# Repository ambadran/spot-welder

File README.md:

Battery Spot Welder Circuit Using Capactive Discharge (CD) Circuit

Using PIC16F628A and 16x2 display, a user-friendly interface is implemented

Three lines of capacitors (six in series) circuit act as the capacitor bank for HIGH
current discharge. They total to a <> Coloumbs.
They have an equivilant series resistance of <> milli-ohms
This means that at 24v they can deliver <> Amps!!!

Four VERY HIGH Power MOSFETs IRF3205 are put in parallel, capable of withstanding <> Amps through them

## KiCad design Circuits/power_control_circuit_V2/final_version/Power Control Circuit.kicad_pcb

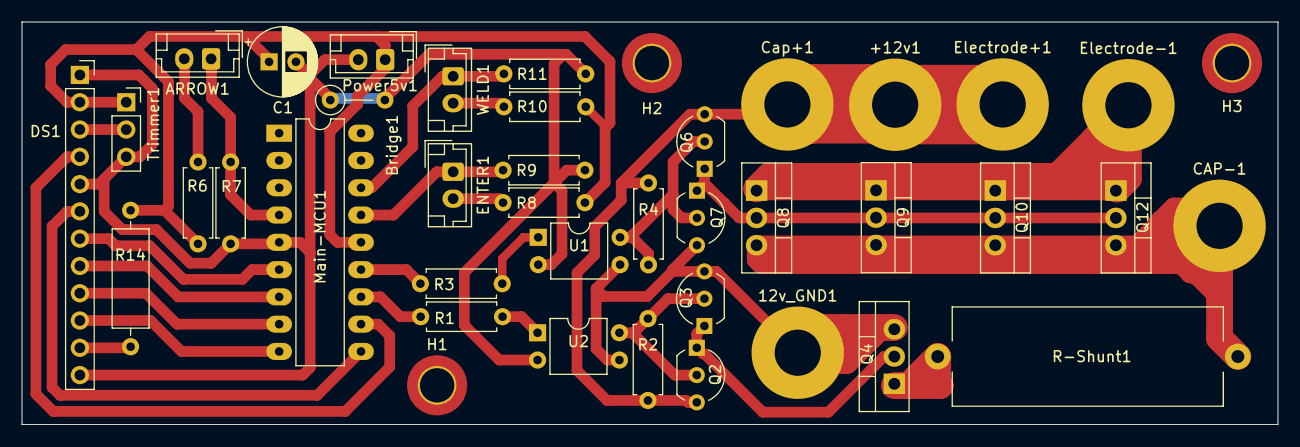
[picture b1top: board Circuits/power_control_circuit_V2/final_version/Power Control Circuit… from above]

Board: 2 copper layers, 116.9 x 37.5 mm, 41 parts (0 on the bottom side), 29 nets.

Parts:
12v_GND1: Pin; MountingHole_4.3mm_M4_Pad
+12v1: Pin; MountingHole_4.3mm_M4_Pad
ARROW1: JST-2P; JST_EH_B2B-EH-A_1x02_P2.50mm_Vertical
Bridge1: 0ohm; R_Axial_DIN0207_L6.3mm_D2.5mm_P5.08mm_Vertical
C1: 220uF; CP_Radial_D6.3mm_P2.50mm
CAP-1: Pin; MountingHole_4.3mm_M4_Pad
Cap+1: Pin; MountingHole_4.3mm_M4_Pad
DS1: WC1602A; PinSocket_1x12_P2.54mm_Vertical
ENTER1: JST-2P; JST_EH_B2B-EH-A_1x02_P2.50mm_Vertical
Electrode+1: Pin; MountingHole_4.3mm_M4_Pad
Electrode-1: Pin; MountingHole_4.3mm_M4_Pad
H1, H2, H3: MountingHole; MountingHole_3.2mm_M3_DIN965_Pad_TopBottom
Main-MCU1: PIC16F628A-IP; DIP-18_W7.62mm_LongPads
Power5v1: JST-2P; JST_EH_B2B-EH-A_1x02_P2.50mm_Vertical
Q2, Q6: S8050; TO-92_Inline_Wide
Q3, Q7: S8550; TO-92_Inline_Wide
Q4, Q8, Q9, Q10, Q12: IRF1405; TO-220-3_Vertical
R1, R3: 220; R_Axial_DIN0207_L6.3mm_D2.5mm_P7.62mm_Horizontal
R2, R4, R6, R8, R10: 1k; R_Axial_DIN0207_L6.3mm_D2.5mm_P7.62mm_Horizontal
R7, R9, R11: 10k; R_Axial_DIN0207_L6.3mm_D2.5mm_P7.62mm_Horizontal
R14: 330; R_Axial_DIN0309_L9.0mm_D3.2mm_P12.70mm_Horizontal
R-Shunt1: 2ohm; R_Axial_Power_L25.0mm_W9.0mm_P27.94mm
Trimmer1: 5kOhm; PinSocket_1x03_P2.54mm_Vertical
U1, U2: PC817; DIP-4_W7.62mm
WELD1: JST-2P; JST_EH_B2B-EH-A_1x02_P2.50mm_Vertical

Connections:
+5V: C1.1, DS1.2 (VDD), Main-MCU1.14 (VDD), Power5v1.1, R6.1, R8.1, R10.1, R14.1, Trimmer1.1
+12V: +12v1.1, Cap+1.1, Electrode+1.1, Q2.3 (C), Q6.3 (C), R2.1, R4.1
/NMOS_CHARGE: Q4.1 (D), R-Shunt1.1
/NMOS_DISCHARGE: Electrode-1.1, Q8.1 (D), Q9.1 (D), Q10.1 (D), Q12.1 (D)
Charging: Main-MCU1.12 (RB6/T1OSC0/T1CKI/PGC), R1.2
D4: DS1.7 (D4), Main-MCU1.6 (RB0/INT)
D5: DS1.8 (D5), Main-MCU1.7 (RB1/RX/DT)
D6: DS1.9 (D6), Main-MCU1.8 (RB2/TX/CK)
D7: DS1.10 (D7), Main-MCU1.9 (RB3/CCP1)
Discharge: Main-MCU1.13 (RB7/T1OSI/PGD), R3.2
EN: DS1.6 (E), Main-MCU1.10 (RB4/PGM)
GND: Bridge1.1, Bridge1.2, C1.2, DS1.1 (VSS), DS1.5 (R/W), DS1.12 (LED(-)), Main-MCU1.5 (VSS), Power5v1.2, R7.2, R9.2, R11.2, Trimmer1.3, U1.2, U2.2
GNDA: 12v_GND1.1, Q3.3 (C), Q4.3 (S), Q7.3 (C), U1.3, U2.3
GNDS: CAP-1.1, Q8.3 (S), Q9.3 (S), Q10.3 (S), Q12.3 (S), R-Shunt1.2
unnamed: ARROW1.2, R6.2
unnamed: DS1.11 (LED(+)), R14.2
unnamed: DS1.3 (VO), Trimmer1.2
unnamed: ENTER1.2, R8.2
unnamed: Q2.2 (B), Q3.2 (B), R2.2, U2.4
unnamed: Q2.1 (E), Q3.1 (E), Q4.2 (G)
unnamed: Q6.2 (B), Q7.2 (B), R4.2, U1.4
unnamed: Q6.1 (E), Q7.1 (E), Q8.2 (G), Q9.2 (G), Q10.2 (G), Q12.2 (G)
unnamed: R1.1, U2.1
unnamed: R3.1, U1.1
unnamed: R10.2, WELD1.2
RS: DS1.4 (RS), Main-MCU1.11 (RB5)
arrowkey: ARROW1.1, Main-MCU1.4 (~MCLR/Vpp/RA5), R7.1
enterkey: ENTER1.1, Main-MCU1.15 (CLKOUT/OSC2/RA6), R9.1
weldingkey: Main-MCU1.16 (CLKIN/OSC1/RA7), R11.1, WELD1.1

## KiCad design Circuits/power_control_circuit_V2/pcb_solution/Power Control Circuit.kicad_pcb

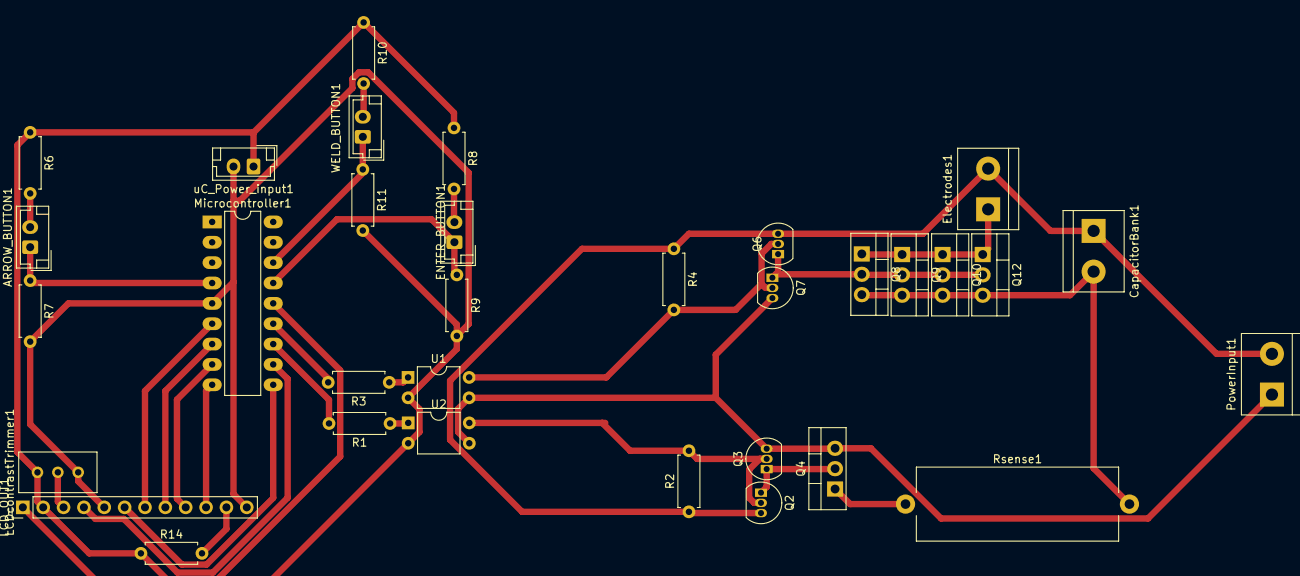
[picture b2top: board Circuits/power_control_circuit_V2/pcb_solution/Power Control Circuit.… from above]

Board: 2 copper layers, 33 parts (0 on the bottom side), 29 nets.

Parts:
ARROW_BUTTON1: Conn_01x02_Socket; JST_EH_B2B-EH-A_1x02_P2.50mm_Vertical
CapacitorBank1: CP; TerminalBlock_bornier-2_P5.08mm
ENTER_BUTTON1: Conn_01x02_Socket; JST_EH_B2B-EH-A_1x02_P2.50mm_Vertical
Electrodes1: Conn_01x02_Male; TerminalBlock_bornier-2_P5.08mm
LCD_OUT1: Conn_01x12_Socket; PinHeader_1x12_P2.54mm_Vertical
LCDcontrastTrimmer1: 5kOhm; Potentiometer_Bourns_3386C_Horizontal
Microcontroller1: PIC16F628A-IP; DIP-18_W7.62mm_LongPads
PowerInput1: Screw_Terminal_01x02; TerminalBlock_bornier-2_P5.08mm
Q2, Q6: S8050; TO-92_Inline
Q3, Q7: S8550; TO-92_Inline
Q4, Q8, Q9, Q10, Q12: IRF1405; TO-220-3_Vertical
R1, R3: 220; R_Axial_DIN0207_L6.3mm_D2.5mm_P7.62mm_Horizontal
R2, R4, R6, R8, R10: 1k; R_Axial_DIN0207_L6.3mm_D2.5mm_P7.62mm_Horizontal
R7, R9, R11: 10k; R_Axial_DIN0207_L6.3mm_D2.5mm_P7.62mm_Horizontal
R14: 330; R_Axial_DIN0207_L6.3mm_D2.5mm_P7.62mm_Horizontal
Rsense1: 1; R_Axial_Power_L25.0mm_W9.0mm_P27.94mm
U1, U2: PC817; DIP-4_W7.62mm
WELD_BUTTON1: Conn_01x02_Socket; JST_EH_B2B-EH-A_1x02_P2.50mm_Vertical
uC_Power_input1: Conn_01x02_Socket; JST_EH_B2B-EH-A_1x02_P2.50mm_Vertical

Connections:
+5V: LCD_OUT1.2, LCDcontrastTrimmer1.1, Microcontroller1.14 (VDD), R6.1, R8.1, R10.1, R14.1, uC_Power_input1.1
+12V: CapacitorBank1.1, Electrodes1.2, PowerInput1.2, Q2.3 (C), Q6.3 (C), R2.1, R4.1
Charging: Microcontroller1.12 (RB6/T1OSC0/T1CKI/PGC), R1.2
D4: LCD_OUT1.7, Microcontroller1.6 (RB0/INT)
D5: LCD_OUT1.8, Microcontroller1.7 (RB1/RX/DT)
D6: LCD_OUT1.9, Microcontroller1.8 (RB2/TX/CK)
D7: LCD_OUT1.10, Microcontroller1.9 (RB3/CCP1)
Discharge: Microcontroller1.13 (RB7/T1OSI/PGD), R3.2
EN: LCD_OUT1.6, Microcontroller1.10 (RB4/PGM)
GND: LCD_OUT1.1, LCD_OUT1.5, LCD_OUT1.12, LCDcontrastTrimmer1.3, Microcontroller1.5 (VSS), R7.2, R9.2, R11.2, U1.2, U2.2, uC_Power_input1.2
GNDA: PowerInput1.1, Q3.3 (C), Q4.3 (S), Q7.3 (C), U1.3, U2.3
GNDS: CapacitorBank1.2, Q8.3 (S), Q9.3 (S), Q10.3 (S), Q12.3 (S), Rsense1.2
LED+: LCD_OUT1.11, R14.2
unnamed: ARROW_BUTTON1.2, R6.2
unnamed: ENTER_BUTTON1.2, R8.2
unnamed: Electrodes1.1, Q8.1 (D), Q9.1 (D), Q10.1 (D), Q12.1 (D)
unnamed: Q2.2 (B), Q3.2 (B), R2.2, U2.4
unnamed: Q2.1 (E), Q3.1 (E), Q4.2 (G)
unnamed: Q4.1 (D), Rsense1.1
unnamed: Q6.2 (B), Q7.2 (B), R4.2, U1.4
unnamed: Q6.1 (E), Q7.1 (E), Q8.2 (G), Q9.2 (G), Q10.2 (G), Q12.2 (G)
unnamed: R1.1, U2.1
unnamed: R3.1, U1.1
unnamed: R10.2, WELD_BUTTON1.2
RS: LCD_OUT1.4, Microcontroller1.11 (RB5)
VO: LCD_OUT1.3, LCDcontrastTrimmer1.2
arrowkey: ARROW_BUTTON1.1, Microcontroller1.4 (~MCLR/Vpp/RA5), R7.1
enterkey: ENTER_BUTTON1.1, Microcontroller1.15 (CLKOUT/OSC2/RA6), R9.1
weldingkey: Microcontroller1.16 (CLKIN/OSC1/RA7), R11.1, WELD_BUTTON1.1

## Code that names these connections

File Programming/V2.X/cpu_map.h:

#ifndef CPU_MAP_H
#define CPU_MAP_H

/* **** LCD PINs **** */
#define LCD_DATA_TRIS TRISB
#define LCD_DATA PORTB
#define D4 RB0
#define D5 RB1
#define D6 RB2
#define D7 RB3
#define EN RB4
#define RS RB5
/* ****************** */

/* *** CD_control pins*** */
#define CHARGE_PIN_TRIS TRISB6
#define CHARGE_PIN RB6
#define DISCHARGE_PIN_TRIS TRISB7
#define DISCHARGE_PIN RB7
/* ********************** */

/* **** button pins**** */
#define BUTTON_TRIS TRISA
#define BUTTON_PORT PORTA

#define ARROW_KEY_TRIS TRISA5
#define ARROW_KEY RA5
#define ARROW_KEY_PIN_NUM 5

#define ENTER_KEY_TRIS TRISA6
#define ENTER_KEY RA6
#define ENTER_KEY_PIN_NUM 6

#define WELD_KEY_TRIS TRISA7
#define WELD_KEY RA7
#define WELD_KEY_PIN_NUM 7
/* ******************** */



#endif

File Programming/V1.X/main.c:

/*
 * File:   main.c
 * Author: ambad
 *
 * Created on April 9, 2021, 11:20 AM
 */


#include <xc.h>
//#include <stdio.h>
#include <stdint.h>
#include <stdbool.h>
#include "config.h"
#include "LCD.h"

#define arrowKey RB7  // the arrow button
#define enterKey RB6  // the enter button
#define weldingButton RA0  // welding activation button
#define discharge RA6
#define charge RA7
uint8_t button1_stat = 0;
bool button2_stat = 0;
bool allow_welding = 0;
uint8_t page = 0;  // program start from page 0
uint8_t choosenValues[1];  // here we will store what the user choosed from the interface
                           // it stores what each page gives in order
                           // first value is 0 or 1, 0 for 0.15mm, and 1 for 0.1mm strip //////

void update(uint8_t button1_tstat, uint8_t button2_stat, uint8_t page_f) {
    
    // page 0 chooses whether battery strip is 0.1 or 0.15mm
    if(page_f == 0) {
        
        // button1 programming as arrow key
        if(button1_tstat >= 2) {
            button1_stat = 0;
        }
        
//        char blah[2];
//        sprintf(blah, "%d", button1_stat);  // using lcd as terminal :))))
        
        char page0_user_input[2][16] = {"0.1mm    0.15mm<", "0.1mm<   0.15mm"};
        LCD_Clear();
        LCD_Set_Cursor(1, 1);
        LCD_Write_String("Strip Depth:");
        LCD_Set_Cursor(2, 1);
        LCD_Write_String(page0_user_input[button1_stat]);
        
        //button2 programming as enter key
        //     since there are only two options so value[0] will be 0 or 1 which is
        //      0.1mm or 0.15mm respectively
        if(button2_stat) {
            choosenValues[0] = button1_tstat;
            button1_stat = 0;
            page = 1;
            LCD_Clear();
            LCD_Set_Cursor(1, 1);
            LCD_Write_String(" Click to start");
            LCD_Set_Cursor(2, 1);
            LCD_Write_String("  Spot weldeing");
        }
    } else if (page_f == 1) {
        LCD_Clear();
        LCD_Set_Cursor(1, 1);
        LCD_Write_String("   Charging..");
        LCD_Set_Cursor(2, 1);
        LCD_Write_String("");
        // turning on the comparator
        CMIE = 1;
        CM2 = 1;
        CM1 = 0;
        CM0 = 1;
    }
}


void main(void) {
    
    //internal oscillator
    OSCF = 1; // 4MHz
    
    //LCD settings
    LCD_Init();
    LCD_Clear();
    LCD_Set_Cursor(1, 1);
    LCD_Write_String("  Battery Spot\0");
    LCD_Set_Cursor(2, 1);
    LCD_Write_String(" Welder    V1.0\0");
    
    //TRIS register
    TRISB6 = 1;  // enter button
    TRISB7 = 1;  // arrow button
    TRISA0 = 1;  // welding activation button
    TRISA7 = 0;  // charge control
    TRISA6 = 0;  // discharge control
    RA7 = 0;  // normally off for both charging and discharging
    RA6 = 0;
    
    //Comparator module
    C2INV = 1;  // inverted, 1 if vin+ < vin-
    CM2 = 1;  // comparator initially off
    CM1 = 1;
    CM0 = 1;
    
    //interrupts
    GIE = 1;
    PEIE = 1;
    
    //Timer
    
    //Main Routine
    while(1) {
        if(arrowKey) {
            button1_stat++;
            update(button1_stat, button2_stat, page);
            __delay_ms(300);
        }
        if(enterKey) {
            button2_stat = ~button2_stat;
            update(button1_stat, button2_stat, page);
            __delay_ms(300);

        }
        if(allow_welding) {
            if(weldingButton) {
                if(choosenValues[0]) { // 1 means 0.1mm
                    discharge = 1;
                    __delay_ms(50);
                    discharge = 0;
                    charge = 1;
                    __delay_ms(300);
                } else {
                    discharge = 1;
                    __delay_ms(100);
                    discharge = 0;
                    charge = 1;
                    __delay_ms(300);
                }
            }
        }
    }
    
    return;
}

void __interrupt() ISR(void) {
    if(CMIF) {
        if(C2OUT) {  // 1 if vin+ < vin-
            discharge = 0; // starting always by closing both charging and discharging
            charge = 0;
            LCD_Clear();
            LCD_Set_Cursor(1, 1);
            LCD_Write_String("    Charged!");
            LCD_Set_Cursor(2, 1);
            LCD_Write_String("");
            allow_welding = 1;
        } else {
            allow_welding = 0;
            LCD_Clear();
            LCD_Set_Cursor(1, 1);
            LCD_Write_String("   Charging..");
            LCD_Set_Cursor(2, 1);
            LCD_Write_String("");
        }
        CMIF = 0;
    }
}

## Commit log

2023-12-19 Uploading V1 from three years ago
2023-12-19 cleaned the files and added .gitignore files
2023-12-19 Created V2 framework
2023-12-19 Almost finished porting lcd.h from V1, still didn't test though
2023-12-21 Major circuit changes and LCD driver finished and tested
2023-12-26 finished and tested Power Electronics, implemented HAL and most MCAL layers
2023-12-30 Further development in Middle-RTOS-layer
2024-01-02 finished Middle and application layer
2024-01-08 minor changes
2024-01-08 finished PCB solution, starting PCB final version|
2024-01-10 further development in V2 final version
2024-01-13 finished PCB final version :)
2024-01-13 added Gcode and BOM for PCB final version
2024-07-03 started pad changes
2024-07-03 added terminal pads to the pcb
2024-07-21 redesigning the circuit
2024-07-22 finished PCB (again)
